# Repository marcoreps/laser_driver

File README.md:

# laser_driver
Energy efficient constant current diode laser driver for CW operation

# Specs
* Input voltage range: 6.5V to 13.8V
* Output voltage range: 0.6V to 2.5V
* Max Output current: 40A to 50A
* Energy efficiency: Around 90% @ Iout > 10A
* Analog input voltage or >500 Hz PWM
* Operating ambient temperature: up to +70°C
* No overshoot
* Protected against reverse-polarity, short-circuit, over-voltage and over-temperature

# Schematic & description

An analog control voltage with 1V/10A or a 5V 500 Hz PWM signal with duty cycle 20%/10A is applied to JP1 and smoothed in a low-pass filter. IC3G$2 is a current shunt amplifier, generating 1V/10A. IC3G$2 compares the input control voltage and the actual output current voltage and drives the DC-DC converters trim pin accordingly. The circuit is an artifically slowed closed control loop because CW laser diodes often cannot take steep current slopes.

# Slope measurement

The displayed schematic is very slow, but guaranteed to never overshoot or oscillate. If desired for capacitors C13 and C14 lower values can be used to make the control loop respond faster. The displayed current waveform shows a start from 0A to 10A. It gets less wiggly when the baseline voltage is set closer to the laser diodes forward voltage, or when the current is not turned off all the way to 0A.

# Baseline Vout setting
Short or connect 0V to JP1, do not leave floating. Measure output voltage and adjust potentiometer R8 to set the baseline Vout to just under forward voltage of your laser diode. Don't make this adjustment while the laser diode is connected, there's a good chance of destroying it.

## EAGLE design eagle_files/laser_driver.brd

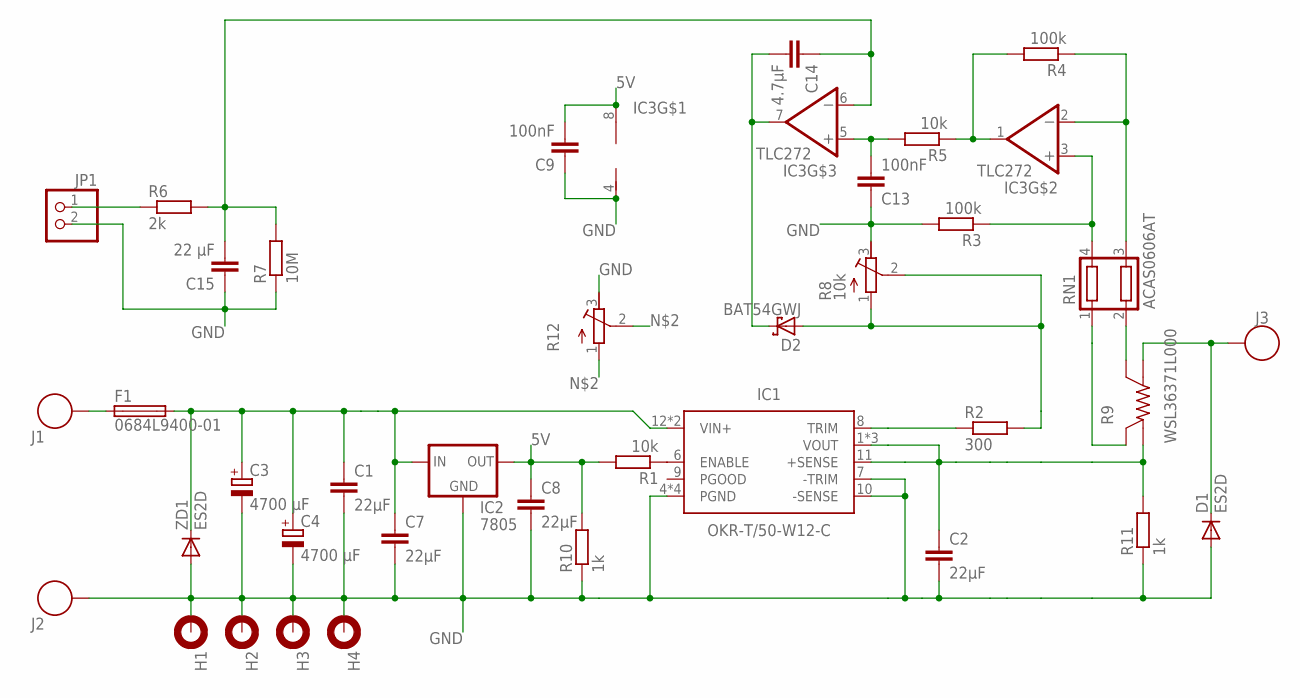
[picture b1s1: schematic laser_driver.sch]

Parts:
C1, C2, C7, C8: 22µF; C0805
C3, C4: 4700 µF; E7,5-16
C9, C13: 100nF; C0805
C14: 4.7µF; C0805
C15: 22 µF; C0805
D1: ES2D; SMB
D2: BAT54GWJ; SOD-123_MINI-SMA
F1: 0684L9400-01; 4818
H1, H2, H3, H4: MOUNT-PAD-ROUND3.0; 3,0-PAD
IC1: OKR-T/50-W12-C
IC2: 7805; TO252
IC3: TLC272; SO08
J1, J2, J3: 74650073R; FBGA90-6X15
JP1: PINHD-1X2; 1X02
R1, R5: 10k; R0805
R2: 300; R0805
R3, R4: 100k; R0805
R6: 2k; R0805
R7: 10M; R0805
R8: 10k; RTRIM64Y
R9: WSL36371L000; WSL3637
R10, R11: 1k; R0805
R12: R-TRIMM4G/J; RTRIM4G/J
RN1: ACAS0606AT; RESCAXS80P160X150X45-4
ZD1: ES2D; SMB

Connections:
5V: C8.1, C9.2, IC2.2 (OUT), IC3.8 (V+), R1.2, R10.2
CV: JP1.1, R6.1
ENABLE: IC1.6 (ENABLE), R1.1
GND: C1.2, C2.2, C3.-, C4.-, C7.2, C8.2, C9.1, C13.1, C15.1, D1.A, H1.B3,0, H2.B3,0, H3.B3,0, H4.B3,0, IC1.4 (PGND), IC1.5 (PGND), IC1.7 (-TRIM), IC1.10 (-SENSE), IC1.14 (PGND), IC1.15 (PGND), IC2.3 (GND), IC3.4 (V-), J2.P$1, J2.P$2, J2.P$3, J2.P$4, JP1.2, R3.2, R7.1, R8.3 (E), R10.1, R11.1, R12.3 (E), ZD1.A
unnamed: D1.C, J3.P$1, J3.P$2, J3.P$3, J3.P$4, R9.I1 (A)
unnamed: D2.A, R2.2, R8.1 (A), R8.2 (S), R12.1 (A), R12.2 (S)
unnamed: C2.1, IC1.1 (VOUT), IC1.2 (VOUT), IC1.3 (VOUT), IC1.11 (+SENSE), R9.I2 (B), R11.2
unnamed: F1.1, J1.P$1, J1.P$2, J1.P$3, J1.P$4
unnamed: R9.V1 (SA), RN1.2
unnamed: IC3.3 (+IN), R3.1, RN1.4
unnamed: R9.V2 (SB), RN1.1
unnamed: IC3.2 (-IN), R4.1, RN1.3
unnamed: IC3.1 (OUT), R4.2, R5.1
unnamed: C13.2, IC3.5 (+IN), R5.2
unnamed: C14.2, D2.C, IC3.7 (OUT)
unnamed: C14.1, C15.2, IC3.6 (-IN), R6.2, R7.2
TRIM: IC1.8 (TRIM), R2.1
VIN: C1.1, C3.+, C4.+, C7.1, F1.2, IC1.12 (VIN+), IC1.13 (VIN+), IC2.1 (IN), ZD1.C

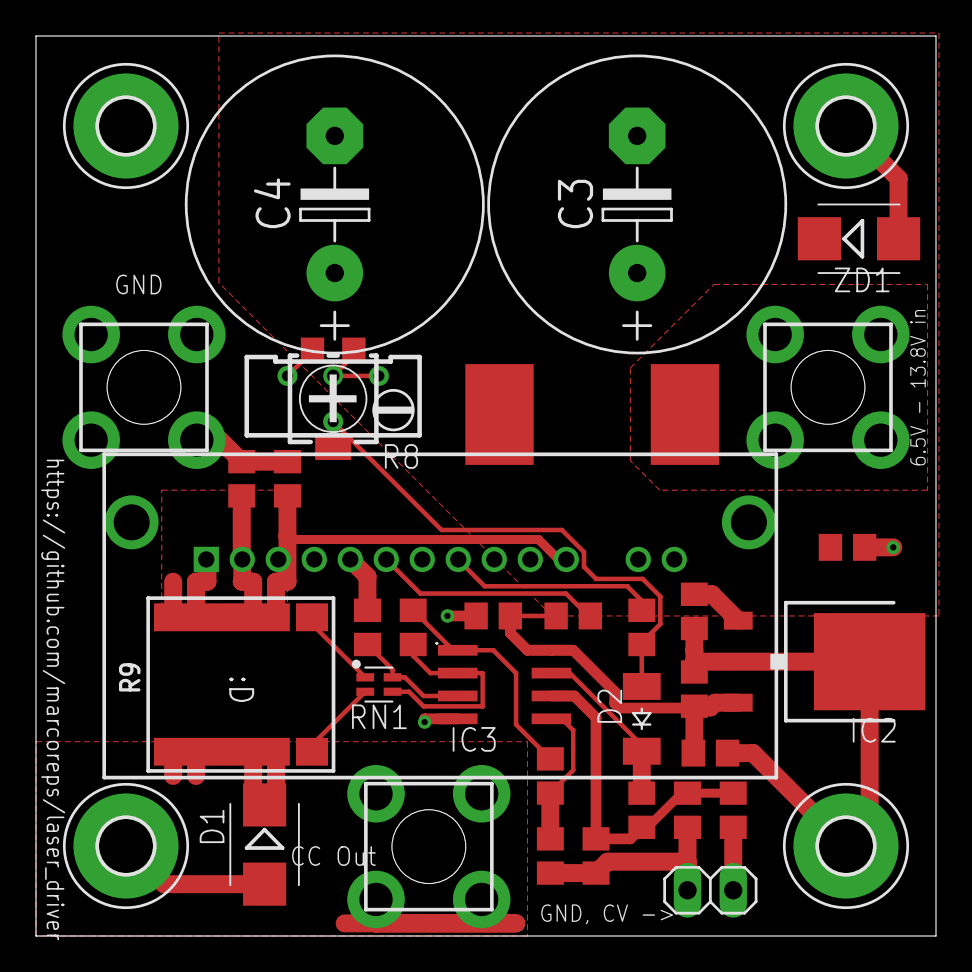
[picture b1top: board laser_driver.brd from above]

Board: 2 copper layers, 50.0 x 50.0 mm, 38 parts (0 on the bottom side), 18 nets.

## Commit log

2018-09-10 Rearrangement
2018-09-10 Cosmetic changes
2018-09-10 Added schematic to readme
2018-09-10 Cleaned up brd after cosmetic changes
2018-09-10 Added details and slope measurement to readme
2018-09-10 Further instructions for the readme
2018-09-10 Elaboration on the wiggly current waveform
2018-09-23 Improved stability, removed useless caps
2018-09-23 Improved component libraries
2018-09-23 Improved silk screen
2018-10-01 Minor changes in component placement after assembly
